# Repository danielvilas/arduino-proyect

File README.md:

arduino-proyect
===============

My Arduino Projects

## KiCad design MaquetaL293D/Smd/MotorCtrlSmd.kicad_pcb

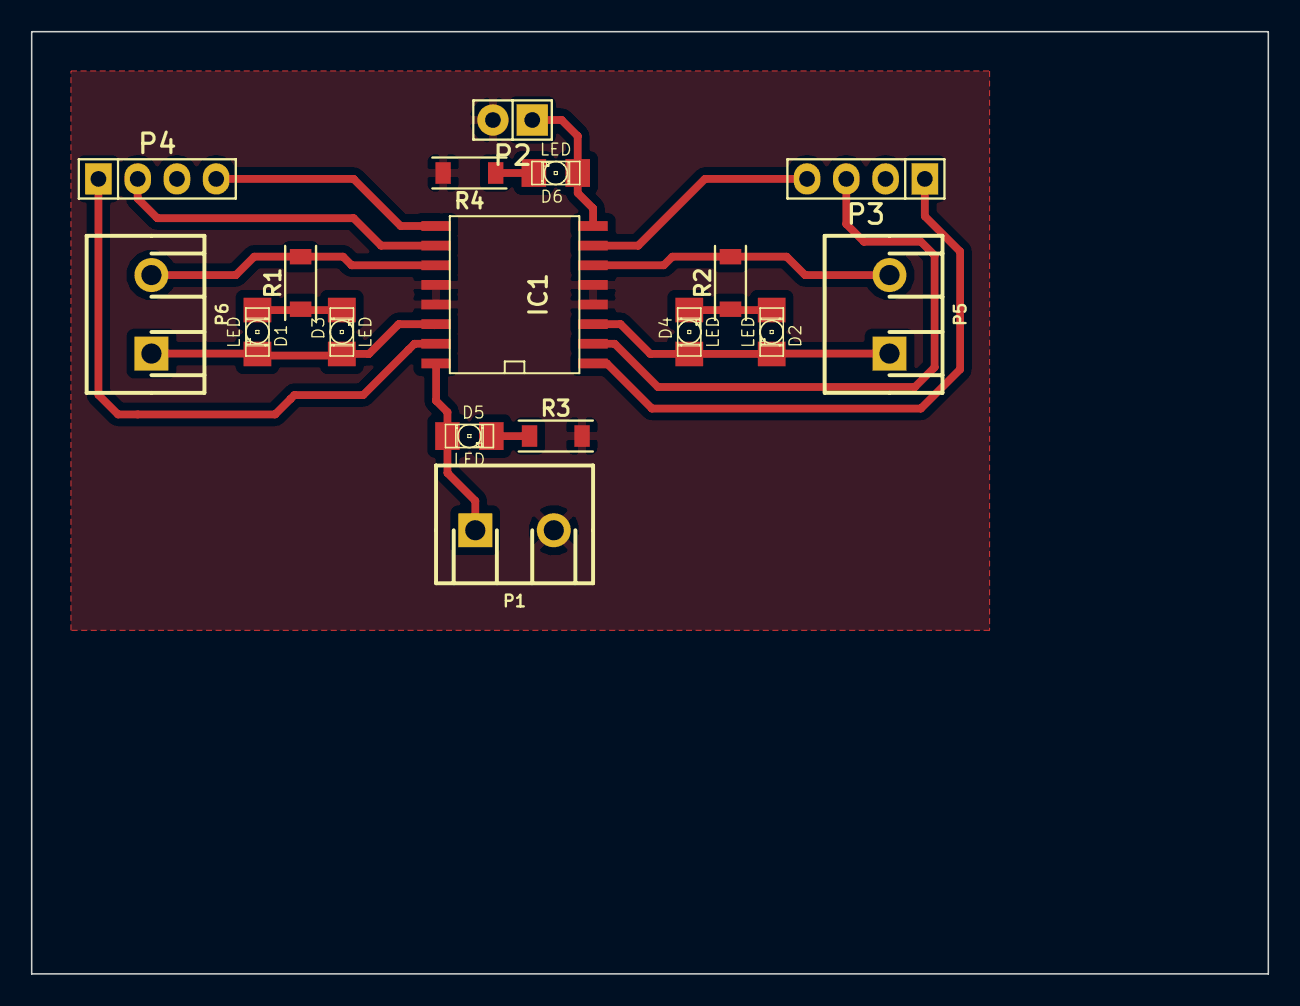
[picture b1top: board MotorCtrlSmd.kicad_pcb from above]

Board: 2 copper layers, 80.0 x 61.0 mm, 17 parts (0 on the bottom side), 17 nets.

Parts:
D1, D2, D3, D4, D5, D6: LED; LED-1206
IC1: L293D; SO-16-L
P1, P5, P6: CONN_01X02; 1x2-SCREW-TERM_P200mil
P2: CONN_01X02; Pin_Header_Straight_1x02
P3, P4: CONN_01X04; Pin_Header_Straight_1x04
R1, R2, R3, R4: R; R_1206

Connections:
+5V: D6.1, IC1.8, P2.1
+12V: D5.1, IC1.16, P1.1
/OuB1: D1.2, D3.1, IC1.14, P6.1
/OutA1: D2.2, D4.1, IC1.3, P5.1
/OutA2: IC1.6, P5.2, R2.2
/OutB2: IC1.11, P6.2, R1.2
GND: IC1.4, IC1.5, IC1.12, IC1.13, P1.2, P2.2, R3.2, R4.2
unnamed: D1.1, D3.2, R1.1
unnamed: D2.1, D4.2, R2.1
unnamed: D5.2, R3.1
unnamed: D6.2, R4.1
unnamed: IC1.1, P3.1
unnamed: IC1.2, P3.3
unnamed: IC1.7, P3.4
unnamed: IC1.9, P4.4
unnamed: IC1.10, P4.2
unnamed: IC1.15, P4.1

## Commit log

2013-12-06 New Proyect
2013-12-06 Improved ramp
2014-01-09 Cambiado para el circuito actual
2014-01-09 Update del circuito
2014-08-03 Comienzo soporte a varios canales
2014-08-05 Actualizacion
2014-08-05 Versiones PCB
2014-08-07 Mejoras Se ha actualizado el schema para el nuevo Fritzing y se ha creado como modulo para 2 canales y dos 595 por canal
2014-08-20 Post de la Fuente
2014-08-21 Circuito para Spice
2014-08-23 Nuevos Circuitos
2014-09-03 Correccion Nodo
2014-09-27 Actualizaciones Varias
2014-11-10 HC06
    Codigo de ejemplo del HC-06 y circuitos Fritzing
2015-06-28 Creación de ArduTrain
2015-07-01 Arrancando BTLE
2015-07-05 Pruebas de lecturas de comandos
    Va un XLS con listado de Funciones a desarrollar
2015-07-07 Mejoras interpretacion msg
2015-07-18 Mejoras proceso
2015-11-14 Nueva Funcionalidad
2015-11-22 Nuevo proyecto para hacer un Horno de soldadura SMD
2015-11-23 Añadido código para leer un Max6675
